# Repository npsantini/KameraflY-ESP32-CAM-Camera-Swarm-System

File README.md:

<div id="top"></div>

# KameraflY

<table width="100%">
    <tr>
	    <td width="33.33%"></td>
	    <td width="33.33%">
		    
	    </td>
	    <td width="33.33%"></td>
    </tr>
</table>

## Contents
- <a href="#firmware">Overview</a>
- <a href="#firmware">ESP32-CAM Firmware</a>
    - <a href="#arduino">Arduino IDE</a>
    - <a href="#libraries">Libraries</a>
    - <a href="#functions">Functions</a>
    - <a href="#firmware-improvement">Potential Improvements</a>
- <a href="#blynk">Blynk App</a>
    - <a href="#setup">Setup</a>
    - <a href="#components">Components</a>
    - <a href="#blynk-improvement">Potential Improvements</a>
- <a href="#web">Web App</a>
    - <a href="#requirements">Requirements</a>
    - <a href="#web-improvement">Potential Improvements</a>
- <a href="#pcb">PCB Info</a>
	- <a href="#pcb-improvement">Potential Improvements</a>
- <a href="#housing">Housing</a>
	- <a href="#housing-improvement">Potential Improvements</a>
- <a href="#parts">Parts</a>
	- <a href="#partslist">Parts List</a>
	- <a href="#parts-improvement">Potential Improvements</a>

<hr>
<!-- Overview -->
<div id="overview"></div>

### Overview
<hr>
<p>
Our current ESP32-CAM camera swarm is a completly wireless swarm that is capable of caturing synchronized images down to 10ms.
The system we have created allows a user to use and Android or iOS app to control the camera swarm. When images are captured they 
are sent to a web server where all of the images can be downloaded at once. The images collected from the web server can be used 
in many different applications like 3D modeling or for use in 3D point cloud software.</p>

<p>Each of our completed modules costs only $13.43. When scaled to 256 modules the cost $6.96 per module. This makes this camera swarm 
an extremely cost effective tool that is a lot more accessible than traditional DSLR focused camera swarms.</p>

<p align="right">(<a href="#top">back to top</a>)</p>
<hr>
<!-- ESP32-CAM Firmware -->
<div id="firmware"></div>

### ESP32-CAM Firmware
<hr>
The ESP32-CAM modules in our swarm were all programmed to work with the Blynk app. This was mainly due to time constraints and the ease of use. It is setup in a way to perform only a few actions like connect to the Blynk app, save images to an SD card, upload an image via FTP, and live stream video. There are improvements that can be made and it's far from perfect. It satisfied our engineering requirements, which is all we had set out to accomplish.

I encourage anyone that would like to continue this to fork this repository or make pull requests.

<div id="arduino"></div>

#### Arduino IDE
The Arduino IDE is what was used for ease of use. It is possible to also use <a href="https://platform.io" target="_blank">PlatformIO</a> although we have not tested it.
It's important to include all of the libraries that you will see in the next section. It is also important that in the change the information in the <a href="#">secrets.h</a> file.
```C++
// secrets.h file
#define SECRET_SSID "INSERT WIFI SSID HERE"
#define SECRET_PASSWORD "INSERT WIFI PASSWORD HERE"

#define SECRET_FTP_SERVER "INSERT FTP SERVER IP ADDRESS HERE"
#define SECRET_FTP_USERNAME "INSERT FTP USERNAME HERE" // ex. user@example.com
#define SECRET_FTP_PASSWORD "INSERT FTP PASSWORD"
```
<div id="libraries"></div>

#### Libraries
In order to include all of the necessary libraries for the ESP32-CAM's you need to 
add the following additional board manager in the Arduino IDE under `File > Preferences`:
<br>
```
https://raw.githubusercontent.com/espressif/arduino-esp32/gh-pages/package_esp32_index.json
```

##### Included packages from the source above:
- SD_MMC
- WebServer
- EEPROM
- FS
- WiFi
- And more.

You might have conflicting wifi libraries. You will have to fix this by removing one of the libraries that the error message lists.

##### Libraries in Arduino Library Manager
- Blynk (Volodymyr Shymanskyy) v0.6.1
- esp32_ftpclient (Leonardo Bispo) v0.1.4
- SD (Arduino) v1.2.4
- Time (Paul Stoffregen) v1.6.1

<div id="functions"></div>

#### Functions
- Live Stream Functions (Anatoli Arkhipenko, https://github.com/arkhipenko/esp32-cam-mjpeg)
	- handle_jpg_stream(void)
	- handle_jpg()
	- handleNotFound()
- SD Card Functions (Rui Santos, https://RandomNerdTutorials.com/esp32-cam-take-photo-save-microsd-card)
	- SD_MMC.begin() // Check to see if sd card is mounted
	- SD_MMC.cardType() // Check card type
- FTP Functions
	- FTP_upload(void)
- Main Logic Functions
	- setup()
	- loop()
	- take_picture()
- Blynk Functions/Methods
	- Blynk.run()
	- BLYNK_CONNECTED()
	- BLYNK_WRITE(V5)
	- BLYNK_WRITE(V10)
	- BLYNK_WRITE(V12)
	- BLYNK_WRITE(V14)
- Misc. Functions
	- deep_sleep()
	- ipAddress2String(const IPAddress& ipAddress)

<div id="firmware-improvement"></div>

#### Potential Improvements

<p>
This firmware for the ESP32-CAM is not perfect. We encourage people make improvements as they see fit. Most of the code is to be specifically used with the Blynk Legacy mobile app. If you wish to use your own app it would need to be changed substantially.
</p>
<p>
One big improvement would be programming the ESP32-CAM modules to take an image at a specified time. This is something we were not able to accomplish with the current version of the Blynk app, but will be coming soon as dicussed in more detail below.
</p>

<p align="right">(<a href="#top">back to top</a>)</p>
<hr>

<!-- Blynk App -->
<div id="blynk"></div>

### Blynk App
<hr>
<p>
We chose to use the Legacy Blynk app to control our ESP32-CAM camera swarm. It's not a perfect solution, but is much more convenient than writing your own app to fulfill the same functionality. There are a lot of great things you can do with the Blynk app, however we have chosen to use what we believe to be the bare essentials necessary to control and effectively use the camera swarm.
</p>

<div id="setup"></div>

#### Setup
<p>Below are some images of the basic setup of each ESP32-CAM module and how to add all of the modules to one tag. In this case, we named the tag "All",
but you could name it whatever you like. Having all of the modules with the same tag allows us to use one button to capture all of the images from each of the cameras in the camera swarm simultaneously.</p>

<table>
    <tr>
        <td width="20%"></td>
        <td width="20%"></td>
        <td width="20%"></td>
        <td width="20%"></td>
        <td width="20%"></td>
    </tr>
    <tr>
	    <td valign="top" width="20%">
		    <p>- Go to "My Devices."</p>
		    <p>- Scroll down and click "+ New Device."</p>
	    </td>
	    <td valign="top" width="20%">
		    <p>- Name the module (numbers help identify the module later).</p>
		    <p>- Select "ESP32 Dev Board.</p>
		    <p>- Choose "Wi-Fi".</p>
		    <p>- Click "Create".</p>
	    </td>
	    <td valign="top" width="20%">
		    <p>- You will then see a list of modules that you have created.</p>
		    <p>- Now create a new tag by clicking "+ New Tag"</p>
	    </td>
	    <td valign="top" width="20%">
		    <p>- Name the tag "All"</p>
		    <p>- Once created check off all of the modules you want to add to the tag.</p>
	    </td>
	    <td valign="top" width="20%">
		    <p>- In the project settings click "Email all" to get all of the Authorization tokens that you will need to include in the firmware.</p>
	    </td>
    </tr>
</table>
<p>
The most important part of the setup is that you get all of the Authorization tokens (emailing them from the app is easiest) and add them to the section of code below. Make sure you only have one authorization token uncommented at a time. For each ESP32-CAM that you program you need to uncomment a new token and change the `cam_module` number to the current module you are using. This will allow you to identify which module each picture came from and helps with troubleshooting the modules.
</p>

```c++
String cam_module = "4"; 
//char auth[] = "MODULE 1 AUTH TOKEN HERE"; //1
//char auth[] = "MODULE 2 AUTH TOKEN HERE"; //2
//char auth[] = "MODULE 3 AUTH TOKEN HERE"; //3
char auth[] = "MODULE 4 AUTH TOKEN HERE"; //4
//char auth[] = "MODULE 5 AUTH TOKEN HERE"; //5
// etc...
```
<div id="components"></div>

#### Components
<p>While we chose to use these specific components to accomplish what we needed to accomplish, you can choose what you you need and can remove the rest. Just make sure to remove the code for components that you aren't using.</p>
<table>
	<tr>
		<td width="40%"></td>
		<td width="60%">
	
- Device Selector

- Slider
	- Target: selector
	- Output: 0 - 4
	- Pin: V10

- Button
	- Target: All tag
	- Output: 0 - 1
	- Pin: V5

- Terminal
	- Target: Selector
	- Add Newline: Yes
	- Autoscroll: Yes
	- Pin: V0

- Video Stream
	- Target: Selector
	- URL: 
	- Pin: V13

- Styled Button (Video Stream Start)
	- Target: Selector
	- Output: 0 - 1
	- Pin: V12

- Styled Button (Video Stream Stop)
	- Target: All tag
	- Output: 0 - 1
	- Pin: V14

- Real-time Clock
	- Timezone: (Whatever you wish to use)

		</td>
	</tr>
</table>

<div id="blynk-improvement"></div>

#### Potential Improvements
<p>There are improvements coming to the Blynk app that will allow for all of the components to be controlled via the Blynk Cloud web dashboard. This would greatly improve the usability and would elimintate the need to use a mobile phone. Being able to send specific signals such as a time in order to schedule an image capture would greatly improve the synchronization times of the images. We have been told that a lot of this functionality should arrive in Q2 2022.
</p>
<p>Until then we highly recommend using the Legacy Blynk app and not the Blynk IoT app.</p>

<p align="right">(<a href="#top">back to top</a>)</p>
<hr>

<!-- Web App -->
<div id="web"></div>

### Web App
<hr>
<p>
The web app that we have included in this is a PHP site displays the last images captured as well as images by each module. It is very basic, but allows you to collect all of the images in a zip file which is extremely useful when you need to import the images in other programs.
</p>

<p>
The login system is something that was added to make sure that people couldn't see the images that were captured unless they had a login. For this specific demo we have a default user and an admin user. Only the admin user has the ability to delete images.
</p>

<p>
<b>It is highly recommended that you change these usernames and passwords!</b>
</p>

- Default User
	- Username: user
	- Password: password

- Admin User
	- Username: admin
	- Password: password

<p>The usernames and passwords are defined as seen below in an array in the `login.php` page and should be changed.</p>

```PHP
$logins = array('admin' => 'password','user' => 'password');
```

<div id="requirements"></div>

#### Requirements

- Web Server
	- Apache
	- PHP v7.0 (or later)
- Optional
	- Web hosting
	- Domain name

<div id="web-improvement"></div>

#### Potential Improvements
<p>A better way of sorting the images would make this a lot better. Right now it relies on the file name of the images to sort them. This is obviously not ideal.</p>

<p align="right">(<a href="#top">back to top</a>)</p>
<hr>

<!-- PCB Info -->
<div id="pcb"></div>

### PCB Info
<hr>
<table>
	<tr>
		<td width="25%"></td>
		<td width="75%">
			<p>The PCB subsystem was created to connect all components used for each module together so they are compact, and set up and transport easily. The PCB reduces the need for wires allowing the casing to be smaller. The PCB has dimensions of 50mm X 55mm. There is a switch in the circuit that will turn power off to the ESP32-CAM saving power.</p>
			<p>The routing on the board connects the output of the battery charger to the battery and then to the boost converter. This will increase the voltage from ~3.7V, the voltage of the battery, to 5V, a useful voltage for the ESP32-CAM. This circuit is also ran through a switch that allows the unit to be put in standby mode to save charge. Another switch is connected to two pins of the ESP32-CAM so they can be shorted out to place the camera in programming mode. The 2-pin header is to provide access to the camera for programming purposes.</p>
		</td>
	</tr>
</table>

<div id="pcb-improvement"></div>

#### Potential Improvements

<p>
We went through 5 different iterations of the PCB which can be found in the `pcb-shematic` folder. Many of the changes from version to version were to make the footprint as small as possible and to make changes to the battery connector. The battery connector is a part that likely needs to be changed with a better connector for the battery we used. Since we couldn't find the exact battery connector we made our own part in Autodesk Eagle.
</p>
<p>
It's highly recommended that you use these PCB schematics as a starting point for your own, unless you use the exact same parts as we did.
</p>
<p align="right">(<a href="#top">back to top</a>)</p>
<hr>

<!-- Housing -->
<div id="housing"></div>

### Housing
<hr>

<table>
	<tr>
		<td width="100%">
			<p>The housing is designed so the ESP32-CAM modules can be easily transported and handled comfortably. The housing includes at least 2 different types of mounting to allow for a variety of ways to setup the system. The two chosen were a Keyhole hanger and two tripod mounts. The case allows for access to the removable battery, the removable SD Card, the charging port for the battery, and the various switches used for power and low power mode. The most recent housing is 72 x 58 x 25 mm which is considered "handheld" and fits the components comfortably.
			</p>
			<p>The drafts of the housing and Autodesk Inventor files can be found in the `ESP32-CAM Housing` folder. 
			</p>
		</td>
	</tr>
	<tr>
		<td width="50%"></td>
	<tr>
</table>

<div id="housing-improvement"></div>

#### Potential Improvements

<p>
The tolerances are really tight with the PCB. This is intentional as it allows the battery to fit against the leaf springs in the battery connector. It is however not as reliable as we would have liked it to be and improvements to the how the battery sits in the housing can and probably should be made.
</p>
<p>
The tolerances between the two pieces of the case are also tight and will likely vary with different 3D printers. This is an area which may need improvement.
</p>

<p align="right">(<a href="#top">back to top</a>)</p>
<hr>

<!-- parts -->
<div id="parts"></div>

### Parts
<hr>
<p>Below is a parts list for all of the different parts required to make the completed product. Most of the items can be found on Amazon, but some are specialty parts like the PCB and battery connector.</p>

<div id="partslist"></div>

<table>
	<tr>
		<th>Device</th>
		<th>Manufacturer</th>
		<th>Item</th>
	</tr>
	<tr>
		<td><a href="https://amzn.to/3pZpIXn" target="_blank">ESP32-CAM</a></td>
		<td>espressif</td>
		<td>Camera Module</td>
	</tr>
	<tr>
		<td><a href="https://amzn.to/3GQk8xg" target="_blank">BP-70A Battery</a></td>
		<td>Kastar</td>
		<td>3.7v Lithium-Ion Camera Battery</td>
	</tr>
	<tr>
		<td><a href="https://amzn.to/3GPXchW" target="_blank">DC-DC Step Up Power Module</a></td>
		<td>Weewooday</td>
		<td>Boost Converter</td>
	</tr>
		<tr>
		<td><a href="https://amzn.to/33BLKIn" target="_blank">TP4056 Charging Module</a></td>
		<td>Weewooday</td>
		<td>Battery charging circuit</td>
	</tr>
	<tr>
		<td><a href="https://amzn.to/3mbGQbh" target="_blank">1.75mm PLA Filament</a></td>
		<td>SUNLU</td>
		<td>Product Housing</td>
	</tr>
	<tr>
		<td><a href="https://amzn.to/3GG7lO2" target="_blank">2 Position Slide Switch</a></td>
		<td>Tnuocke</td>
		<td>Power/Programming switch</td>
	</tr>
	<tr>
		<td><a href="https://jlcpcb.com" target="_blank">Custom PCB</a></td>
		<td>jlcpcb.com</td>
		<td>PCB for each module</td>
	</tr>
	<tr>
		<td><a href="https://amzn.to/3mbpr2y" target="_blank">8-Pin Socket Connectors</a></td>
		<td>Comidox</td>
		<td>Headers for ESP32-CAM</td>
	</tr>
		<tr>
		<td><a href="https://www.te.com/usa-en/product-1746142-1.html" target="_blank">3-Pin Leaf Type Connector (1746142-1)</a></td>
		<td>TE Connectivity</td>
		<td>Battery Connector</td>
	</tr>
</table>

<div id="parts-improvement"></div>

#### Potential Improvements

<p>The boost converter that we used easy extremly sensitive to heat therefor hard to solder without destroying it. It is recommended that is be switched out for a more durable and reliable boost converter.</p>
<p>
The battery connector is not meant to be used with the specific battery we are using. It is close to being the right one and will work, but it is recommneded that you find a better connector if you plan to use that same battery.
</p>

<p align="right">(<a href="#top">back to top</a>)</p>

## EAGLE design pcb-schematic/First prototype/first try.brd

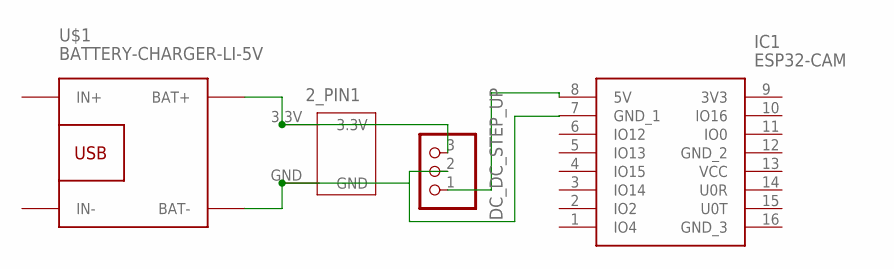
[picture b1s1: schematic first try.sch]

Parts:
2_PIN1: 2_PIN_HEADER
DC_DC_STEP_UP: PINHD-1X3; 1X03
IC1: ESP32-CAM; ESP32CAM
U$1: BATTERY-CHARGER-LI-5V

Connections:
unnamed: 2_PIN1.GND, DC_DC_STEP_UP.2, IC1.7 (GND_1), U$1.BAT-
unnamed: 2_PIN1.3.3V, DC_DC_STEP_UP.3, U$1.BAT+
unnamed: DC_DC_STEP_UP.1, IC1.8 (5V)

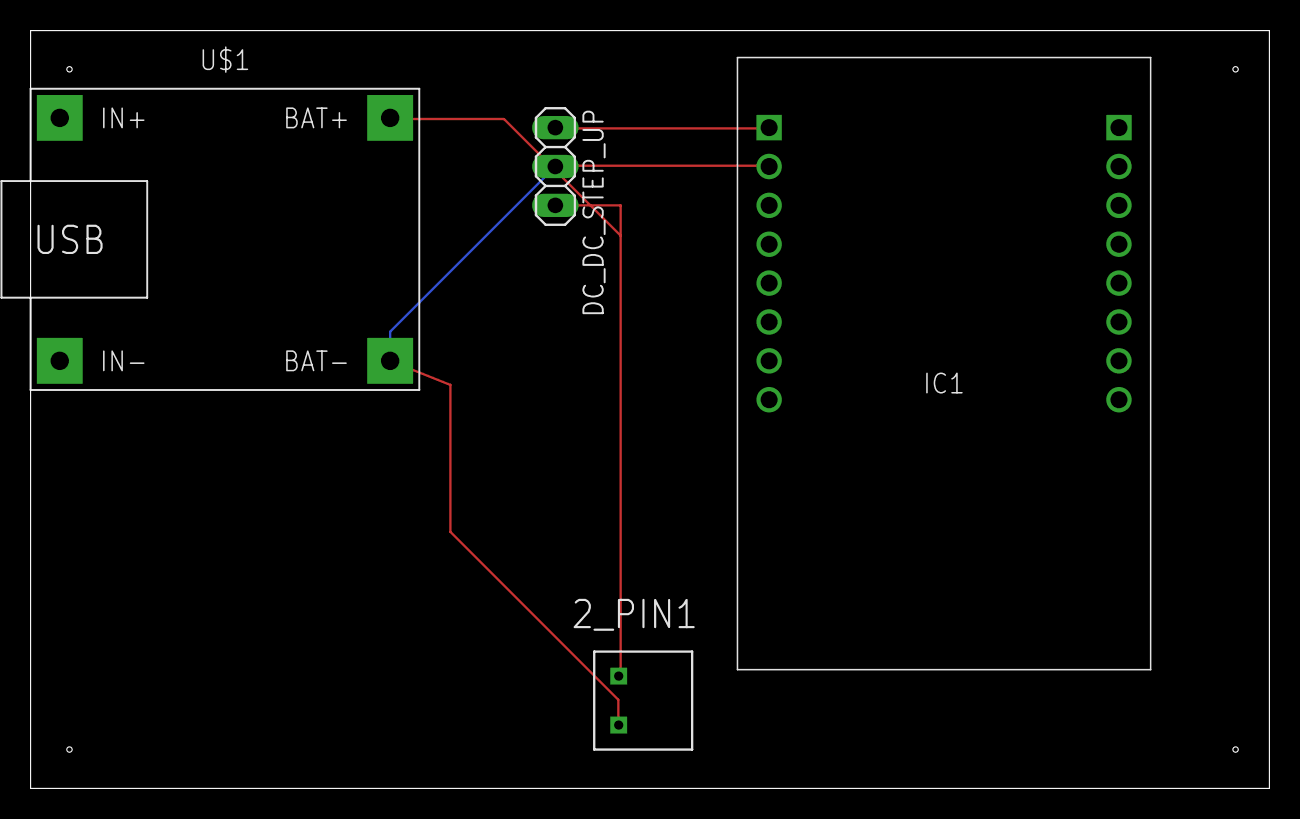
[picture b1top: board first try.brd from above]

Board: 2 copper layers, 81.0 x 49.5 mm, 4 parts (0 on the bottom side), 3 nets.

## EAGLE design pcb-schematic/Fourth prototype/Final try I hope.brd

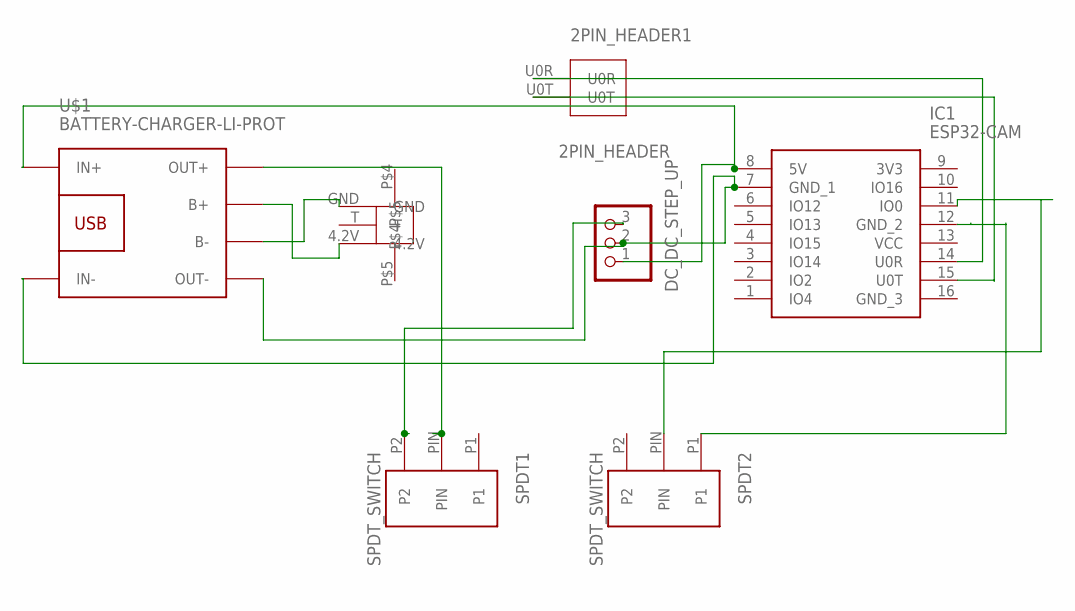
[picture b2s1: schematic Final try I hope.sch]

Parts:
2PIN_HEADER1: 2PIN_HEADER
DC_DC_STEP_UP: PINHD-1X3; 1X03
IC1: ESP32-CAM; ESP32CAM
SPDT1, SPDT2: SPDT_SWITCH
U$1: BATTERY-CHARGER-LI-PROT
U$2: BATTERY_CONNECTOR

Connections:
unnamed: DC_DC_STEP_UP.1, IC1.8 (5V), U$1.IN+
unnamed: DC_DC_STEP_UP.3, SPDT1.P2
unnamed: U$1.B-, U$2.GND
unnamed: U$1.B+, U$2.4.2V
unnamed: IC1.11 (IO0), SPDT2.PIN
unnamed: IC1.12 (GND_2), SPDT2.P1
unnamed: 2PIN_HEADER1.U0R, IC1.14 (U0R)
unnamed: 2PIN_HEADER1.U0T, IC1.15 (U0T)
unnamed: SPDT1.PIN, U$1.OUT+
unnamed: DC_DC_STEP_UP.2, IC1.7 (GND_1), U$1.IN-, U$1.OUT-

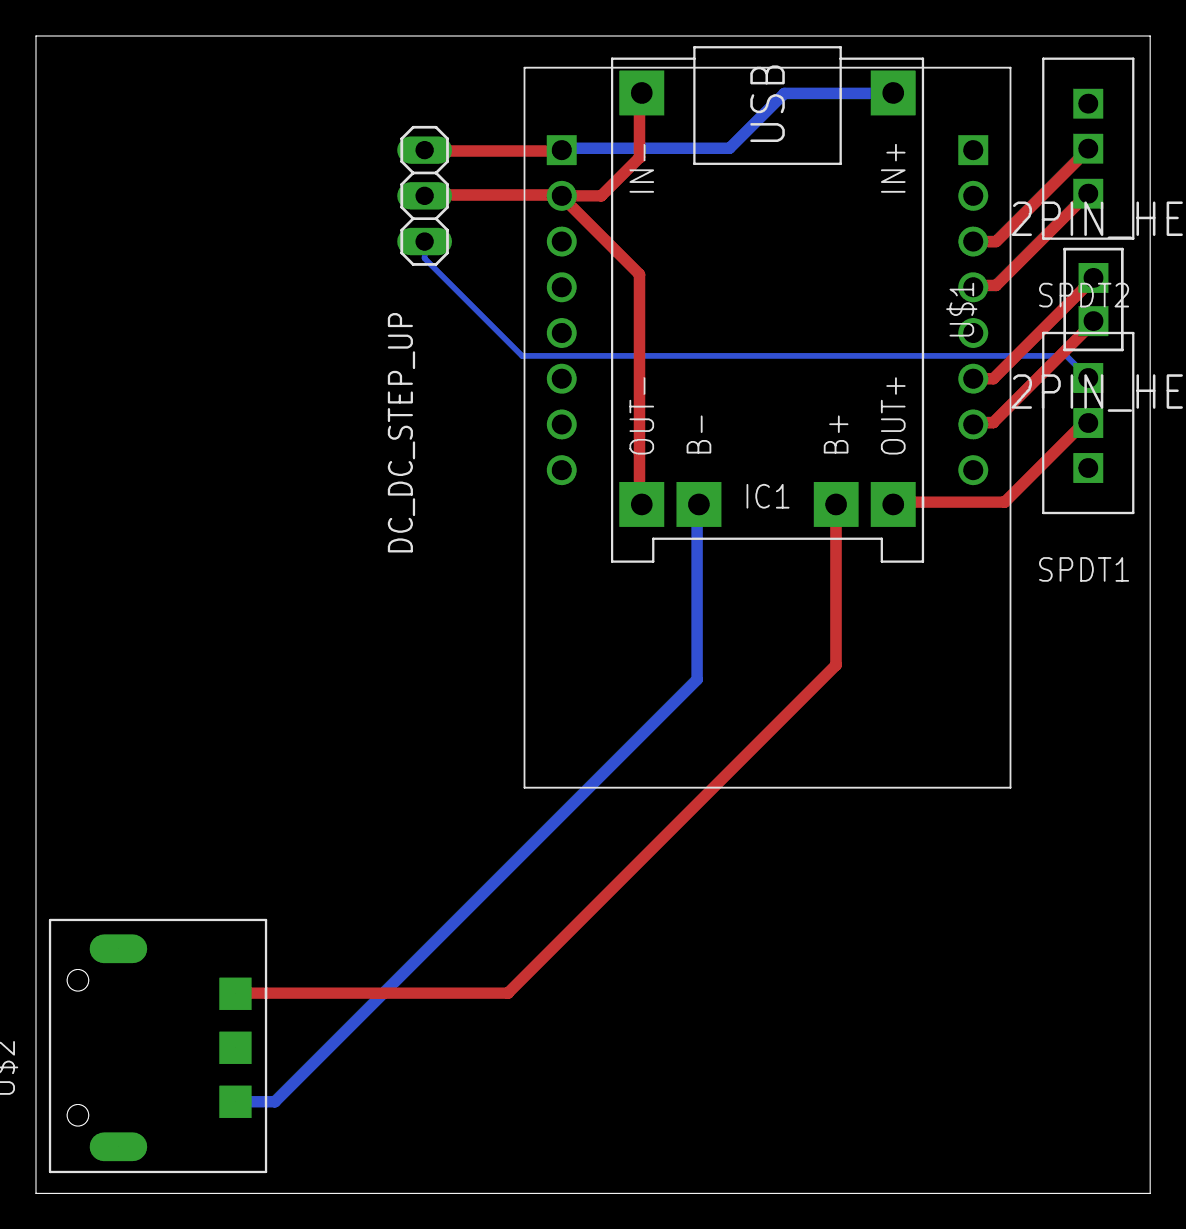
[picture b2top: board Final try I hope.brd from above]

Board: 2 copper layers, 61.9 x 64.3 mm, 7 parts (0 on the bottom side), 10 nets.

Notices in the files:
parts and their libraries:
diy-modules: Released under the Creative Commons Attribution 4.0 International License: http://creativecommons.org/licenses/by/4.0
